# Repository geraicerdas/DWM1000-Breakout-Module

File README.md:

### Repository Content
* **/hardware** : Schematic files (.pdf) and Eagle design files (.sch and .brd)
* **/production** : gerber file for pcb manufacturing

You can purchase this product from  

# DWM1000-Breakout-Module
DWM1000 Breakout Module with Voltage Level

This is modified version of the original designed by [prototyping-corner](https://github.com/prototyping-corner/DWM1000-Breakout). Because hard to find TXB0108DQSR chip, so we made change it to TXB0108PWR. Several decoupling capacitor is also added to filter out voltage spikes and pass through only the DC component of the signal

If you want to make your self, just download the gerber file in production folder. Send it to your fav pcb manufacturer. And dont forget to get the Bill of materials :
|Qty | Part Name | Parts | MPN |
| ------------- |:-------------|:-------------| -----:|
| 1 | DWM1000 | U2 | |
| 1 | TXB0108PWR | U3 | |
| 3 | SMD LED 0805 RED | L1, L2, L3 | |
| 3 | 1K ohm Resistor 0603 | R3, R4, R7 | |
| 5 | 10K ohm Resistor 0603 | R1, R2, R5, R6, R8 | |
| 4 | 100nF Capacitor 0603 | C1, C2, C3, C4 | |

## License
*We invests time and resources providing this open-source hardware, please support us by purchasing our products.*

*Designed by **[Insan Sains](https://www.youtube.com/insansains)** for **[Gerai Cerdas](https://geraicerdas.com)**, with contributions from the open source community. Creative Commons Attribution/Share-Alike, all text above must be included in any redistribution. See license.txt for additional information.*

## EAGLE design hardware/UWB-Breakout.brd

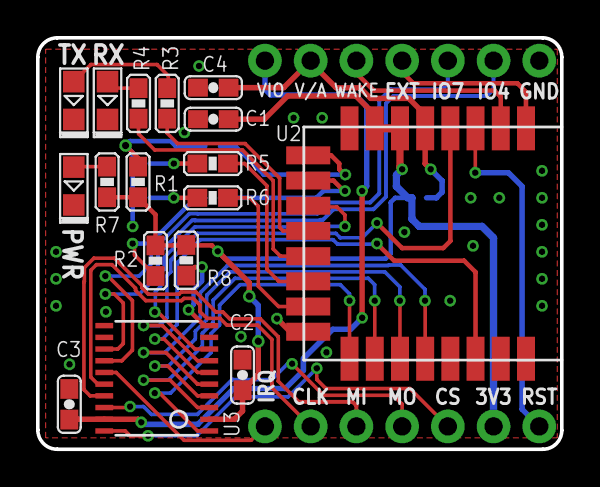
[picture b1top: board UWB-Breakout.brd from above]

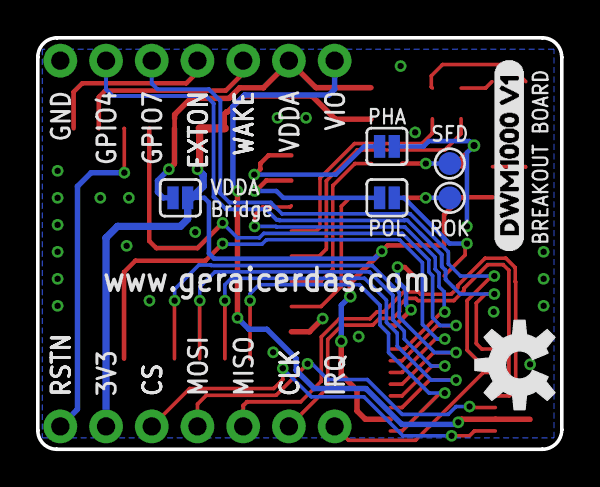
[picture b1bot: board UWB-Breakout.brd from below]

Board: 2 copper layers, 29.1 x 22.9 mm, 27 parts (7 on the bottom side), 35 nets.

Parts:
C1, C2, C3, C4: 100n; C0603
FRAME1: FRAME; A4-HOR
J1, J2: 1X07_NO_SILK
JP1: SPIPHA; SMT-JUMPER_2_NO_SILK
JP2: SPIPOL; SMT-JUMPER_2_NO_SILK
JP3: JUMPER-SMT_2_NO_SILK; SMT-JUMPER_2_NO_SILK
L1, L2, L3: LED0805
LOGO1: OSHW-LOGOM; OSHW-LOGO-M
R1, R2, R5, R6: 5K1; R0603
R3, R4, R7: 1K; R0603
R8: R0603
TP1, TP2: TEST-POINT3X5; PAD.03X.05
U2: DWM1000; XCVR_DWM1000
U3: TSSOP20
U$1: DWM1000_V10

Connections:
3.3V: C1.2, C2.2, J2.6, JP3.1, R1.1, R2.1, R7.2, R8.1, U2.6, U2.7, U3.2
CLK: J2.2, U3.16
CS: J2.5, U3.20
DWM_CLK: U2.20, U3.5
DWM_CS: U2.17, U3.1
DWM_GPIO4: U2.11, U3.8
DWM_GPIO7: U2.4, U3.7
DWM_IRQ: U2.22, U3.6
DWM_MISO: U2.19, U3.4
DWM_MOSI: U2.18, U3.3
EXTON: J1.4, U2.1
GND: C1.1, C2.1, C3.1, C4.1, J1.7, L1.C, L2.C, L3.C, U2.8, U2.16, U2.21, U2.23, U2.24, U3.11
GPIO4: J1.6, U3.13
GPIO7: J1.5, U3.14
IRQ: J2.1, U3.15
MISO: J2.3, U3.17
MOSI: J2.4, U3.18
unnamed: L1.A, R7.1
unnamed: L3.A, R3.1
unnamed: JP1.2, U2.9
unnamed: JP2.2, U2.10
unnamed: JP1.1, R1.2
unnamed: JP2.1, R2.2
unnamed: R6.1, TP2.P$1
unnamed: R5.1, TP1.P$1
unnamed: L2.A, R4.1
unnamed: R8.2, U3.10
RSTN: J2.7, U2.3
RXOK_LED: R6.2, U2.15
RX_LED: R4.2, U2.13
SFD_LED: R5.2, U2.14
TX_LED: R3.2, U2.12
VDD: C4.2, J1.2, JP3.2, U2.5
VIO: C3.2, J1.1, U3.19
WAKEUP: J1.3, U2.2

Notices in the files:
parts and their libraries:
SparkFun-Connectors: Licensing: Creative Commons ShareAlike 4.0 International - https://creativecommons.org/licenses/by-sa/4.0
